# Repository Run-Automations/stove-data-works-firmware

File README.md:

# Run Automations — EPC Monitor Firmware

**Platform:** STM32F103C8T6 (BluePill) · **Programmer:** ST-Link V2 · **Flash tool:** STM32CubeProgrammer

---

## Table of Contents

1. [Hardware Overview](#1-hardware-overview)
2. [Prerequisites](#2-prerequisites)
3. [Before You Flash](#3-before-you-flash)
4. [Burning Firmware via ST-Link](#4-burning-firmware-via-st-link)
   - 4.1 [Wiring the ST-Link](#41-wiring-the-st-link)
   - 4.2 [Flashing with STM32CubeProgrammer](#42-flashing-with-stm32cubeprogrammer)
5. [First Boot Checklist](#5-first-boot-checklist)
6. [How the Device Works](#6-how-the-device-works)
7. [Troubleshooting](#7-troubleshooting)

---

## 1. Hardware Overview

| Component | Role |
|---|---|
| STM32F103C8T6 (BluePill) | Main microcontroller |
| SIM800L | GSM/GPRS modem — data upload and device identity |
| PZEM004T v3.0 | AC voltage, current and power measurement |
| GPS module | Location tagging |
| Relay | Remote switch control driven by the portal |

---

## 2. Prerequisites

- **Device registered on the Run Automations portal** — the IMEI of the SIM800L on the board must be registered on the portal before the board is powered on. See [§3 Before You Flash](#3-before-you-flash).
- **ST-Link V2** USB programmer (clone or genuine)
- **STM32CubeProgrammer** — [download from ST](https://www.st.com/en/development-tools/stm32cubeprog.html)
- ST-Link USB driver installed (Windows: run the driver installer bundled with STM32CubeProgrammer; Linux/macOS: libusb — usually automatic)
- Pre-built firmware binary: `epc_monitor.bin` (supplied by Run Automations)

---

## 3. Before You Flash

> ⚠️ **This step is mandatory. Do not skip it.**

Each board is bound to the Run Automations platform using the unique IMEI of its SIM800L module. The device cannot connect to the server or upload any data unless its IMEI has been registered on the portal first.

### Steps

1. **Find the IMEI.** The IMEI is a 15-digit number printed on a sticker on the SIM800L module. Note it down before assembling the enclosure.

2. **Log in to the Run Automations portal** and navigate to **Devices → Add Device**.

3. **Create a new device** and fill in:
   - **Device type:** EPC Monitor
   - **IMEI:** the 15-digit number from the SIM800L on this specific board
   - **Label / name:** a recognisable identifier for the deployment site

4. **Save the device** on the portal.

5. Only after saving should you proceed to flash and power on the board.

> **One board — one registration.** Every physical board has a unique SIM800L with a unique IMEI. Never register the same IMEI for more than one device entry.

---

## 4. Burning Firmware via ST-Link

### 4.1 Wiring the ST-Link

Connect the ST-Link V2 to the BluePill's **SWD header** (4-pin connector on the short end of the board):

```
ST-Link V2          BluePill SWD Header
─────────────────   ───────────────────
SWDIO  (pin 2)  →   SWDIO
SWDCLK (pin 6)  →   SWDCLK
GND    (pin 4)  →   GND
3.3V   (pin 8)  →   3V3   ← power the board from the programmer
```

> **Important:** Power the BluePill from the ST-Link's 3.3 V pin only — do **not** connect a separate 5 V USB supply at the same time.

Ensure the **BOOT0 jumper** is set to **0** (GND side). This is the default position for normal operation. Do not change it.

---

### 4.2 Flashing with STM32CubeProgrammer

1. Open **STM32CubeProgrammer**.
2. In the top-right connection panel set:
   - Interface: **ST-LINK**
   - Mode: **SWD**
   - Speed: **4000 kHz**
3. Click **Connect**. The device information panel should populate with the chip UID and flash size.
4. Go to the **Erasing & Programming** tab (rocket icon, left sidebar).
5. Configure the options:
   - **File path:** browse to `epc_monitor.bin`
   - **Start address:** `0x08000000`
   - ☑ **Verify programming**
   - ☑ **Run after programming**
6. Click **Start Programming**.

A successful flash looks like this in the log panel:

```
Memory Programming ...
File          : epc_monitor.bin
Size          : xx KB
Address       : 0x08000000

Programming...
████████████████████████ 100%

Verifying ...
████████████████████████ 100%

File download complete
Time elapsed: x.xx s
Start operation achieved successfully
```

The board resets automatically and begins running the firmware.

> **Connection fails?** Hold the **RESET** button on the BluePill, click **Connect** in CubeProgrammer, then release RESET. This forces a connect-under-reset.

---

## 5. First Boot Checklist

After flashing, connect a serial monitor at **115200 baud** to the debug port on the board and power it on. Within approximately 60 seconds you should see:

```
Run Automations — EPC Monitor
System ready.
```

If the device does not reach **System ready** within 2 minutes, refer to the [Troubleshooting](#7-troubleshooting) section.

Once the device is running, verify it appears as **online** in the Run Automations portal under the device entry you created in §3. The portal will begin receiving readings shortly after.

---

## 6. How the Device Works

The EPC Monitor is a self-contained field device. Once deployed and powered, it operates fully autonomously without any user interaction.

On boot the device connects to the mobile data network, authenticates with the Run Automations platform using its hardware identity, and begins monitoring the connected appliance. It periodically transmits readings — including power consumption, GPS location, and appliance status — to the platform. The relay output is controlled remotely from the portal in response to each transmission.

The device automatically detects the start and end of a cooking session based on power draw, and handles network interruptions and power cuts gracefully without losing session data.

All operational parameters are set at the factory in the firmware binary. No field configuration is required or possible beyond registering the device on the portal as described in §3.

---

## 7. Troubleshooting

**ST-Link not detected by CubeProgrammer**
- Reinstall ST-Link USB drivers from the driver folder inside the STM32CubeProgrammer installation directory.
- Try connect-under-reset: hold RESET on the BluePill, click Connect, then release RESET.
- ST-Link clones occasionally deliver low voltage — if the chip UID does not appear, power the BluePill from an external 3.3 V supply instead.

**"No target connected" during programming**
- Check that SWDIO and SWDCLK are not swapped.
- BOOT0 jumper must be at position **0** (GND side).
- On some BluePill clones the SWD interface is unresponsive if the board was previously running firmware. Hold RESET throughout the entire connect and program sequence.

**Device does not reach "System ready" after flashing**
- Confirm the SIM card is inserted and has an active data plan.
- Confirm the IMEI was registered on the portal before powering on (§3).
- Check that the SIM800L module is correctly seated and its power supply is stable.

**Device is online but shows no readings on the portal**
- Verify the GPS antenna has line of sight to the sky — indoor deployments may show zero coordinates until a fix is acquired.
- Confirm the PZEM sensor is connected to a live AC supply. The sensor requires AC on its measurement terminals to respond.

**Authentication failure shown in debug output**
- The IMEI on the SIM800L does not match any registered device on the portal. Re-check the IMEI and update or create the device entry in the portal.
- Confirm the SIM's APN setting matches the mobile operator in the deployment region. Contact Run Automations support if the APN needs to be updated.

**Relay not responding to portal commands**
- Confirm the relay wiring is intact and the coil supply voltage is correct.
- The relay follows commands from the portal only — it cannot be toggled locally.

---

*For support contact Run Automations. Do not attempt to modify or re-flash the firmware binary — doing so voids device support and will break platform authentication.*

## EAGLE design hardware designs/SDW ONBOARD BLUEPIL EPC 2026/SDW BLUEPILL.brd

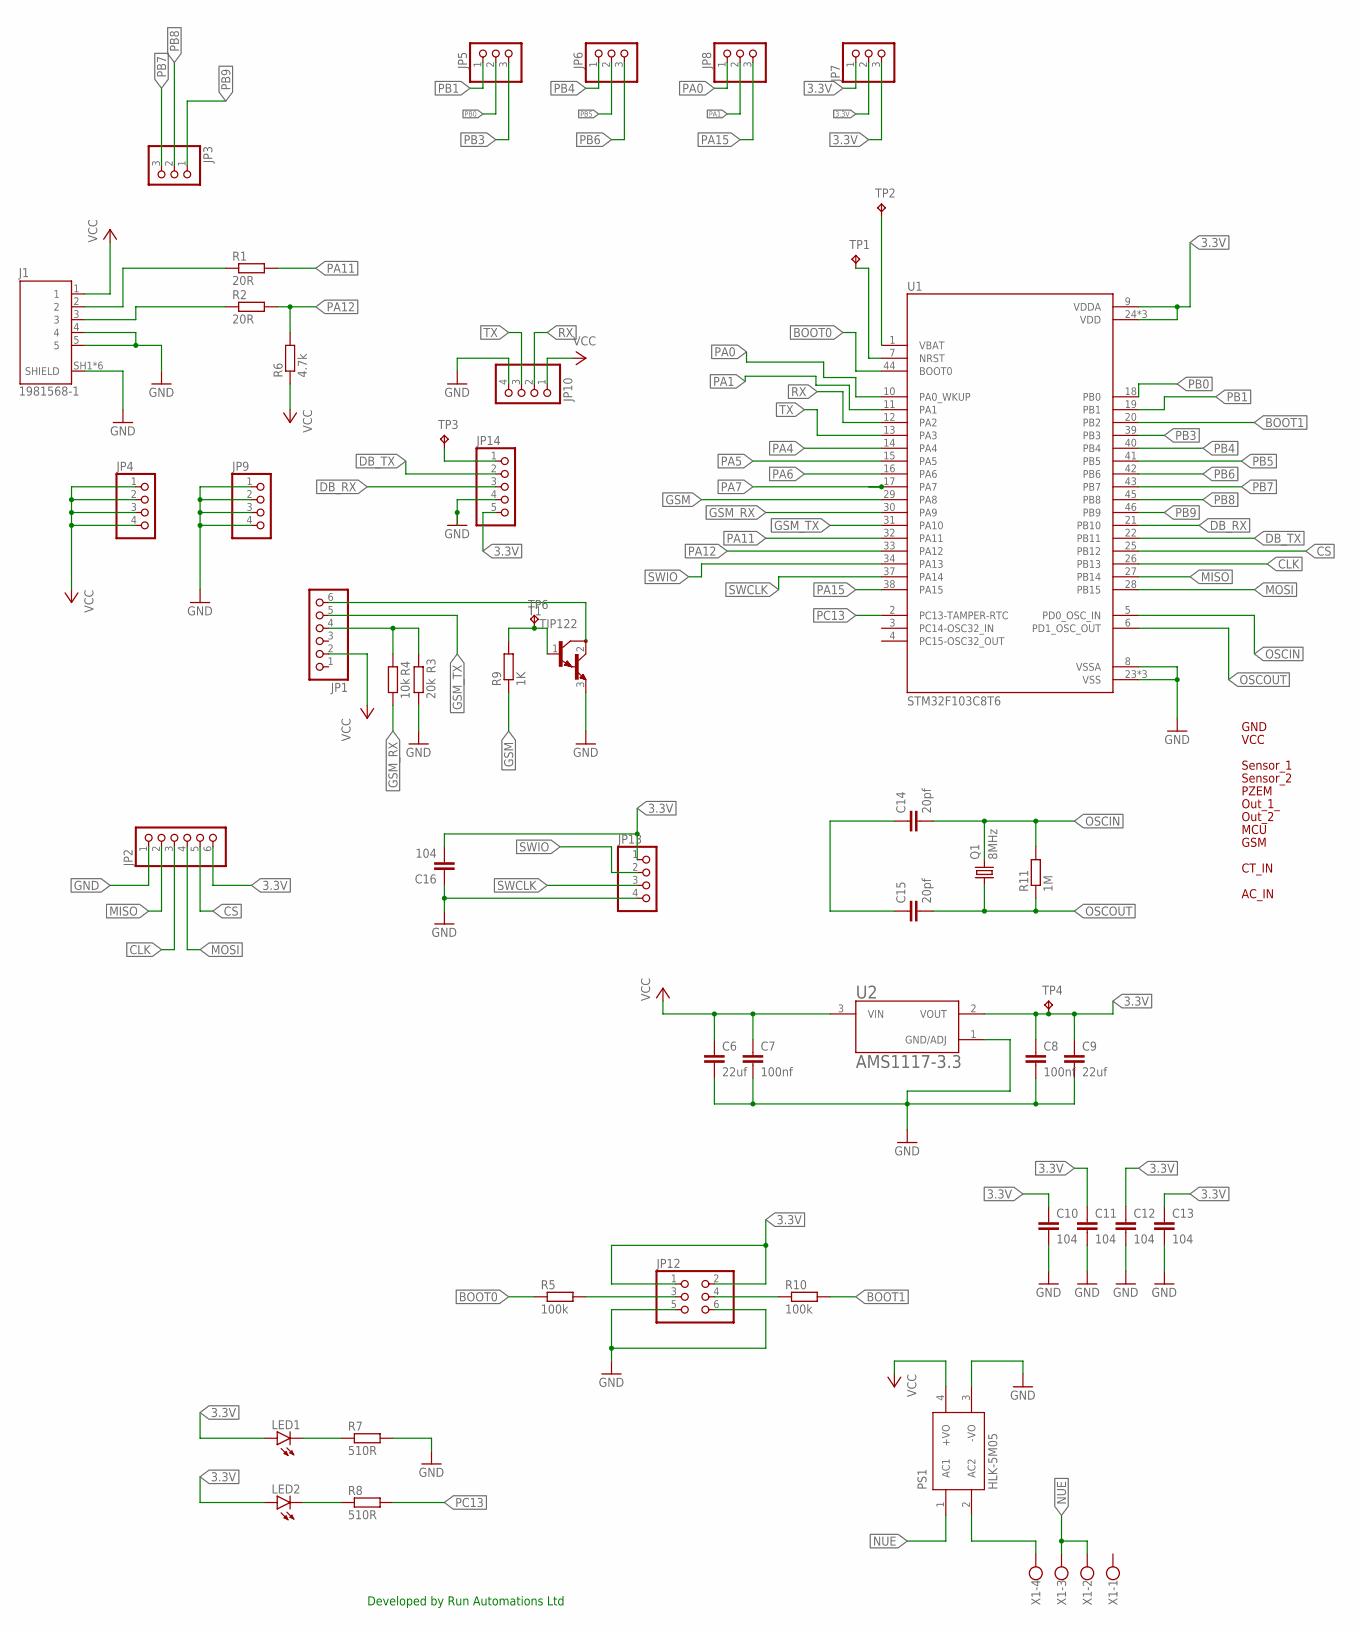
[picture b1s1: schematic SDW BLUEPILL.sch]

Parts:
C6, C9: 22uf; C0805
C7, C8: 100nf; C0805
C10, C11, C12, C13, C16: 104; C0805
C14, C15: 20pf; C0805
J1: 1981568-1; TE_1981568-1
JP1, JP2: PINHD-1X6; 1X06
JP3, JP5, JP6, JP7, JP8: PINHD-1X3; 1X03
JP4, JP9, JP10: PINHD-1X4; 1X04
JP12: PINHD-2X3; 2X03
JP13: PINHD-1X4/90; 1X04/90
JP14: PINHD-1X5; 1X05
LED1, LED2: LEDCHIPLED_0805; CHIPLED_0805
PS1: HLK-5M05; CONV_HLK-5M05
Q1: 8MHz; HC49/S
R1, R2: 20R; M0805
R3: 20k; M0805
R4: 10k; M0805
R5, R10: 100k; M0805
R6: 4.7k; M0805
R7, R8: 510R; M0805
R9: 1K; M0805
R11: 1M; M0805
T1: TIP122; TO220
TP1, TP2, TP3, TP4, TP6: TPB1,27; B1,27
U1: STM32F103C8T6; QFP50P900X900X160-48N
U2: AMS1117-3.3; SOT229P700X180-4N
U$2: VCC0
U$3: GND0
U$5: SENSOR_10
U$6: SENSOR_20
U$7: PZEM0
U$8: OUT_1_0
U$9: OUT_20
U$10: MCU0
U$11: GSM0
U$13: CT_IN0
U$15: AC_IN0
X1: W237-4

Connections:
3.3V: C8.1, C9.1, C10.1, C11.1, C12.1, C13.1, C16.2, JP2.6, JP7.1, JP7.2, JP7.3, JP12.1, JP12.2, JP13.1, JP14.5, LED1.A, LED2.A, TP4.TP, U1.9 (VDDA), U1.24 (VDD), U1.36 (VDD), U1.48 (VDD), U2.2 (VOUT)
BOOT0: R5.1, U1.44 (BOOT0)
BOOT1: R10.2, U1.20 (PB2)
CLK: JP2.3, U1.26 (PB13)
CS: JP2.5, U1.25 (PB12)
DB_RX: JP14.3, U1.21 (PB10)
DB_TX: JP14.2, U1.22 (PB11)
GND: C6.2, C7.2, C8.2, C9.2, C10.2, C11.2, C12.2, C13.2, C16.1, J1.4, J1.5, J1.SH1 (SHIELD), J1.SH2 (SHIELD), J1.SH3 (SHIELD), J1.SH4 (SHIELD), J1.SH5 (SHIELD), J1.SH6 (SHIELD), JP2.1, JP9.1, JP9.2, JP9.3, JP9.4, JP10.4, JP12.5, JP12.6, JP13.4, JP14.4, PS1.3 (-VO), R3.1, R7.2, T1.3 (E), U1.8 (VSSA), U1.23 (VSS), U1.35 (VSS), U1.47 (VSS), U2.1 (GND/ADJ)
GSM: R9.1, U1.29 (PA8)
GSM_RX: R4.1, U1.30 (PA9)
GSM_TX: JP1.5, U1.31 (PA10)
MISO: JP2.2, U1.27 (PB14)
MOSI: JP2.4, U1.28 (PB15)
unnamed: PS1.2 (AC2), X1.4
unnamed: J1.2, R1.1
unnamed: JP1.6, T1.2 (C)
unnamed: JP1.4, R3.2, R4.2
unnamed: R9.2, T1.1 (B), TP6.TP
unnamed: LED1.C, R7.1
unnamed: J1.3, R2.1
unnamed: LED2.C, R8.1
unnamed: JP12.3, R5.2
unnamed: JP12.4, R10.1
unnamed: C14.1, C15.1
unnamed: TP2.TP, U1.1 (VBAT)
unnamed: TP1.TP, U1.7 (NRST)
unnamed: JP14.1, TP3.TP
NUE: PS1.1 (AC1), X1.2, X1.3
OSCIN: C14.2, Q1.2, R11.2, U1.5 (PD0_OSC_IN)
OSCOUT: C15.2, Q1.1, R11.1, U1.6 (PD1_OSC_OUT)
PA0: JP8.1, U1.10 (PA0_WKUP)
PA1: JP8.2, U1.11 (PA1)
PA4: U1.14 (PA4)
PA5: U1.15 (PA5)
PA6: U1.16 (PA6)
PA7: U1.17 (PA7)
PA11: R1.2, U1.32 (PA11)
PA12: R2.2, R6.2, U1.33 (PA12)
PA15: JP8.3, U1.38 (PA15)
PB0: JP5.2, U1.18 (PB0)
PB1: JP5.1, U1.19 (PB1)
PB3: JP5.3, U1.39 (PB3)
PB4: JP6.1, U1.40 (PB4)
PB5: JP6.2, U1.41 (PB5)
PB6: JP6.3, U1.42 (PB6)
PB7: JP3.3, U1.43 (PB7)
PB8: JP3.2, U1.45 (PB8)
PB9: JP3.1, U1.46 (PB9)
PC13: R8.2, U1.2 (PC13-TAMPER-RTC)
RX: JP10.2, U1.12 (PA2)
SWCLK: JP13.3, U1.37 (PA14)
SWIO: JP13.2, U1.34 (PA13)
TX: JP10.3, U1.13 (PA3)
VCC: C6.1, C7.1, J1.1, JP1.2, JP4.1, JP4.2, JP4.3, JP4.4, JP10.1, PS1.4 (+VO), R6.1, U2.3 (VIN)

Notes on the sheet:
Developed by Run Automations Ltd

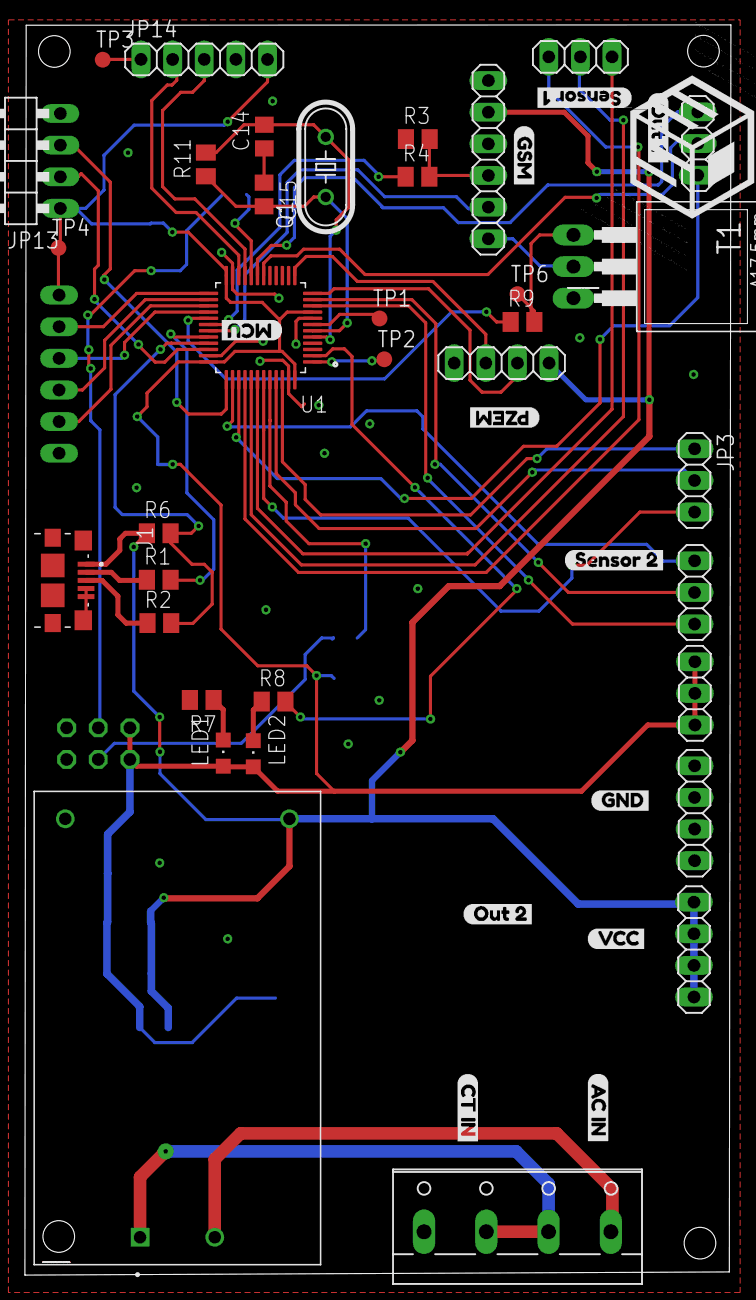
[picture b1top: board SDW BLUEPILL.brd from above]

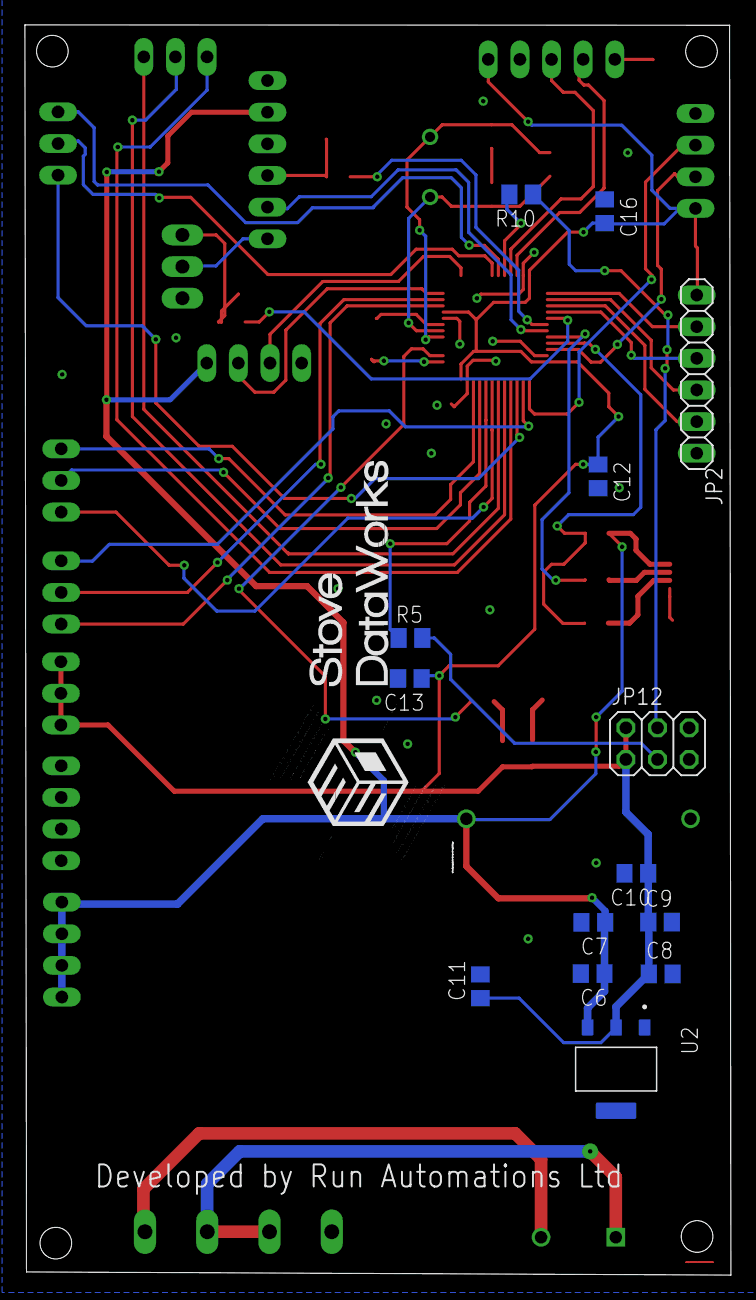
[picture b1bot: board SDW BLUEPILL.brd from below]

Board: 2 copper layers, 56.7 x 100.4 mm, 60 parts (14 on the bottom side), 50 nets.
